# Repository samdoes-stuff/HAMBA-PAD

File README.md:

# HAMBA-PAD
This is my macropad!
# Features
 6 Cherry MX keys 1 Rotary Encoder with switch 1 I2C display

# Before We Begin

🐄 Because Tomorrow is Eid... 🎉
I couldn't just commit code — I had to commit to a cow.

While you're deploying apps, I'm deploying livestock.
While you're pushing to main, I'm pushing hay to a very judgmental bovine.

Yes, tomorrow is Eid, and I bought a cow.
And not just any cow — this one moo-ved my heart and inspired my repo structure.

Now featuring:

CAD files shaped like beefy dreams 🛠️

Rotary encoders spinning faster than uncles after 3 cups of Eid tea ☕

More moo than you can git pull 🐄

| Feature                | Fusion 360 CAD                        | Cow                                            | Reality Check                                                  |
| ---------------------- | ------------------------------------- | ---------------------------------------------- | -------------------------------------------------------------- |
| **Shape**              | Perfectly parametric, clean curves    | Curves? More like squiggles & wobbles          | Fusion 360 tries to model squiggles; cow just wobbles for fun! |
| **Behavior**           | Obeys every command, no complaints    | Randomly moos, eats grass, naps a lot          | Cow wins in chill vibes; Fusion 360 wins in “do what I say.”   |
| **Flexibility**        | Can stretch or compress with a click  | Stretches? Only when someone calls dinner time | CAD models obey physics; cows obey hunger.                     |
| **Sound**              | Silent unless you count your keyboard | Loud moos, occasional tail swishes             | Sorry Fusion 360, cows have better volume control.             |
| **Energy consumption** | Requires electricity & caffeine       | Eats grass, naps, and still looks majestic     | Cow is the original eco-friendly machine.                      |
| **Rotary involvement** | Rotates perfectly on digital axes     | Tail rotates randomly, usually to swat flies   | Cow’s rotary = natural antenna; CAD rotary = pure precision.   |

Stretch Goals (because why not?)
Design a cow-shaped Eid lantern with Fusion 360 — because everyone needs a glowing moo at night.

Create a rotary encoder that controls the volume of a virtual cow’s moo. Extra points for adding echo! 🐄🎶

Animate a Fusion 360 model that “stretches” like a cow trying to reach the last bite of grass.

# Schematic

# PCB

# CAD

# Firmware
Used KMK but have not decided yet.

# BOM
1 SEEED XIAO RP2040

6 Cherry MX switch

1 EC11 Rotary encoder

1 0.91 inch OLED display

Eid Mubarak! 🎉
May your Eid be joyful, your cows happy, and your rotary encoders never jam!

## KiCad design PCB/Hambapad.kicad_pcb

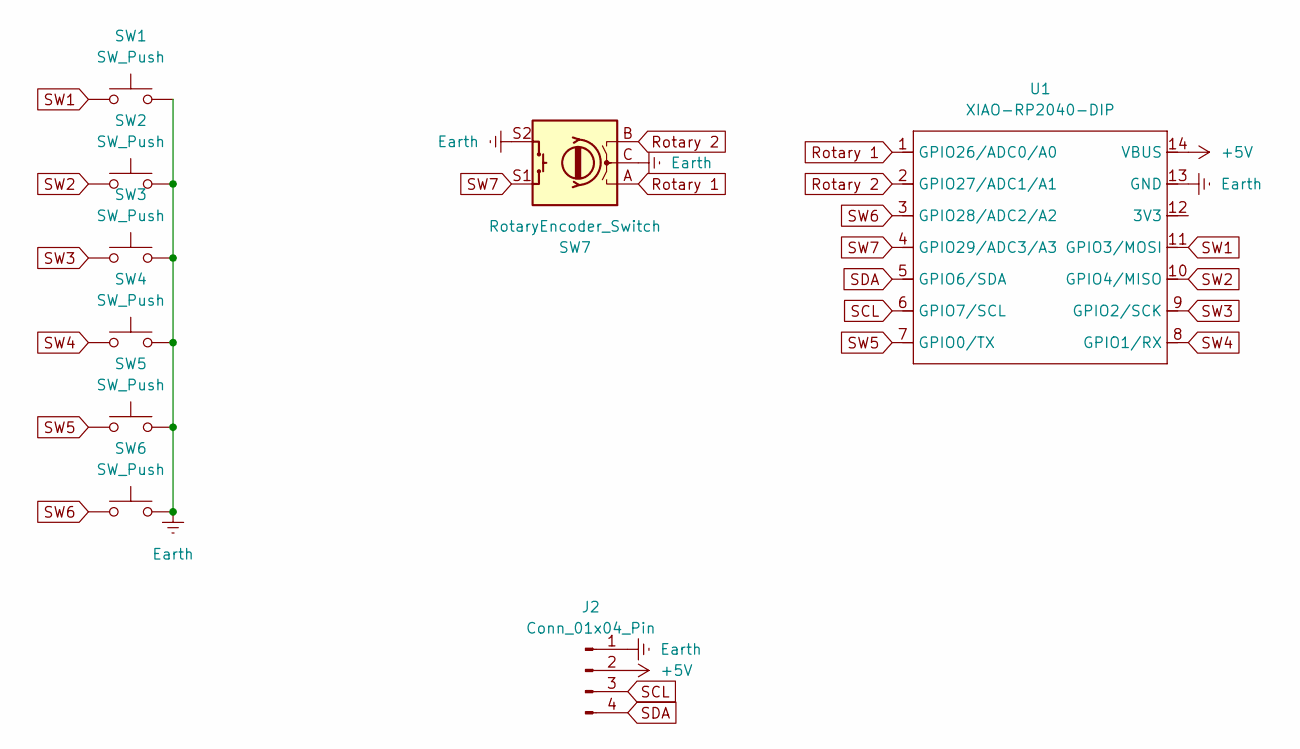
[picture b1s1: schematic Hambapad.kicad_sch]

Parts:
J2: Conn_01x04_Pin; NS-Tech_Grove_1x04_P2mm_Vertical
SW1, SW2, SW3, SW4, SW5, SW6: SW_Push; SW_Cherry_MX_1.00u_PCB
SW7: RotaryEncoder_Switch; RotaryEncoder_Alps_EC11E-Switch_Vertical_H20mm
U1: XIAO-RP2040-DIP

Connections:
+5V: J2.2, U1.14 (VBUS)
Earth: J2.1, SW1.2, SW2.2, SW3.2, SW4.2, SW5.2, SW6.2, SW7.C, SW7.S2, U1.13 (GND)
Rotary 1: SW7.A, U1.1 (GPIO26/ADC0/A0)
Rotary 2: SW7.B, U1.2 (GPIO27/ADC1/A1)
SCL: J2.3, U1.6 (GPIO7/SCL)
SDA: J2.4, U1.5 (GPIO6/SDA)
SW1: SW1.1, U1.11 (GPIO3/MOSI)
SW2: SW2.1, U1.10 (GPIO4/MISO)
SW3: SW3.1, U1.9 (GPIO2/SCK)
SW4: SW4.1, U1.8 (GPIO1/RX)
SW5: SW5.1, U1.7 (GPIO0/TX)
SW6: SW6.1, U1.3 (GPIO28/ADC2/A2)
SW7: SW7.S1, U1.4 (GPIO29/ADC3/A3)

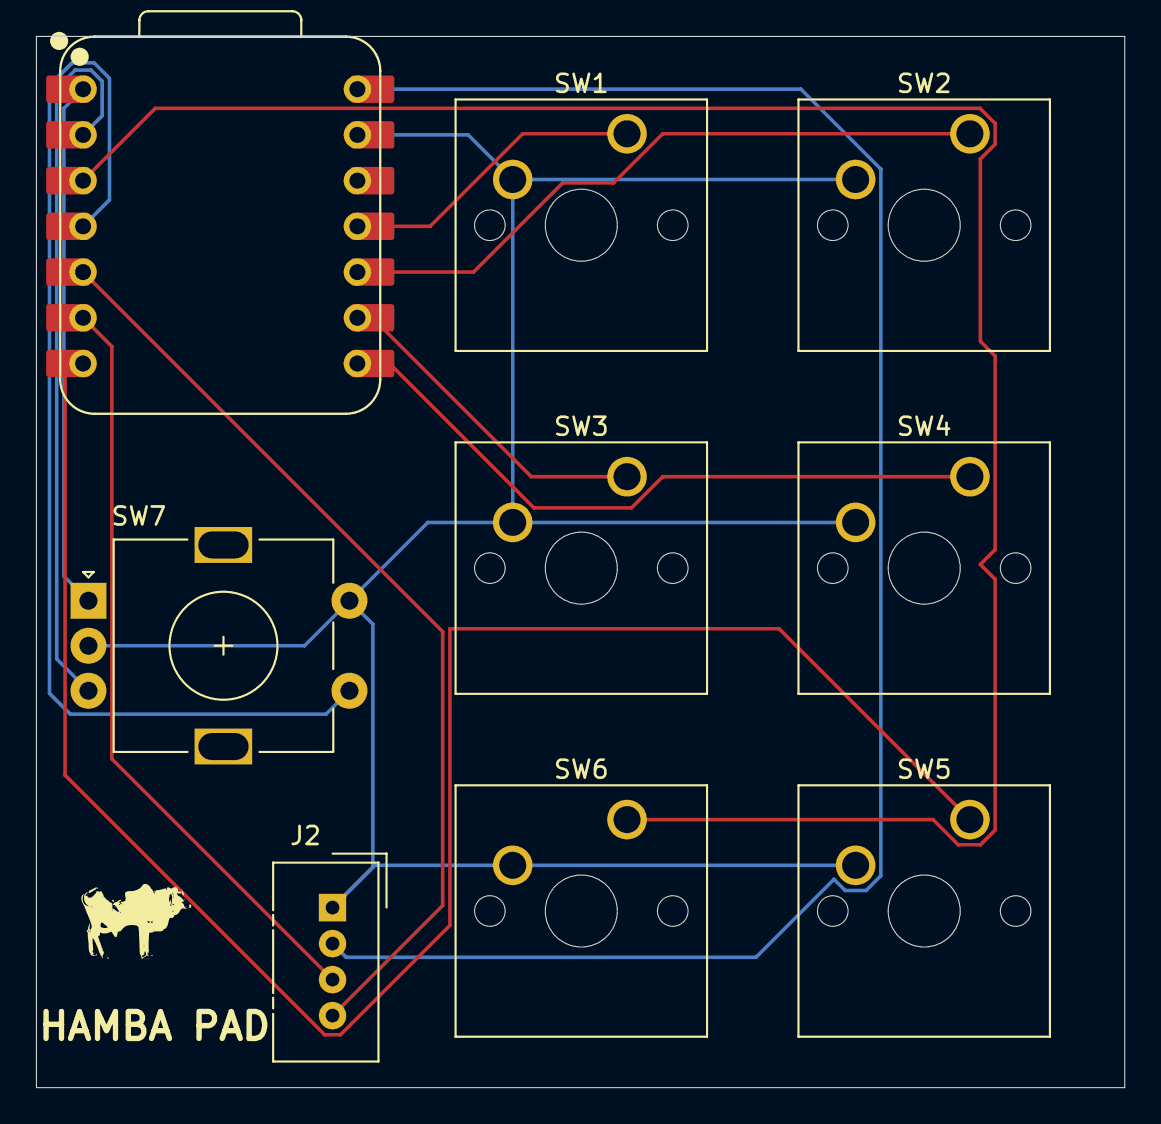
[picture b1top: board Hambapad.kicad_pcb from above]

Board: 2 copper layers, 60.5 x 58.4 mm, 9 parts (0 on the bottom side), 13 nets.

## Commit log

2025-06-06 README.md
2025-06-06 Create CAD
2025-06-06 Create Schematic
2025-06-06 Schematic.svg
2025-06-06 Gerber.zip
2025-06-06 Create 00
